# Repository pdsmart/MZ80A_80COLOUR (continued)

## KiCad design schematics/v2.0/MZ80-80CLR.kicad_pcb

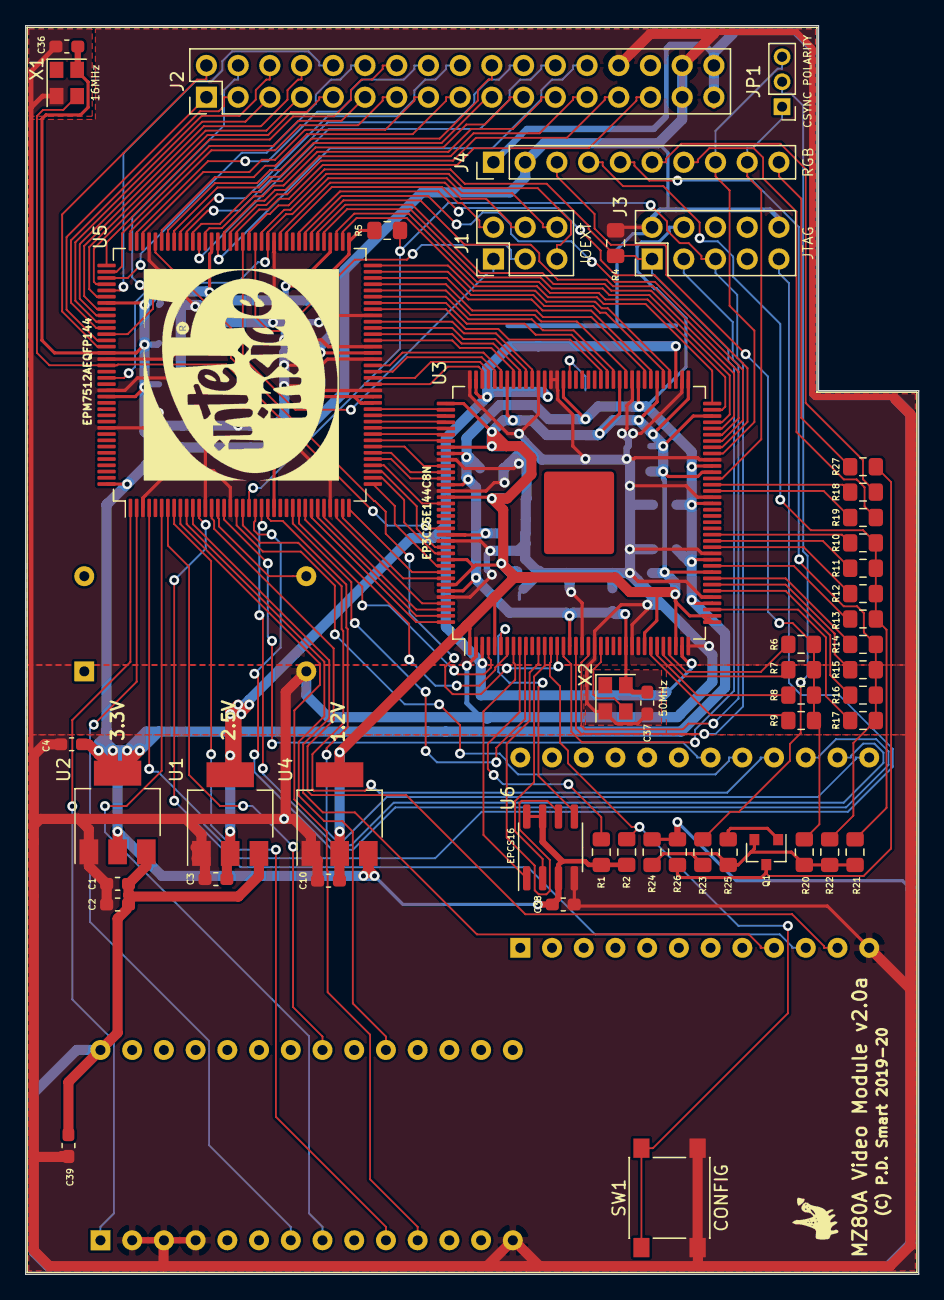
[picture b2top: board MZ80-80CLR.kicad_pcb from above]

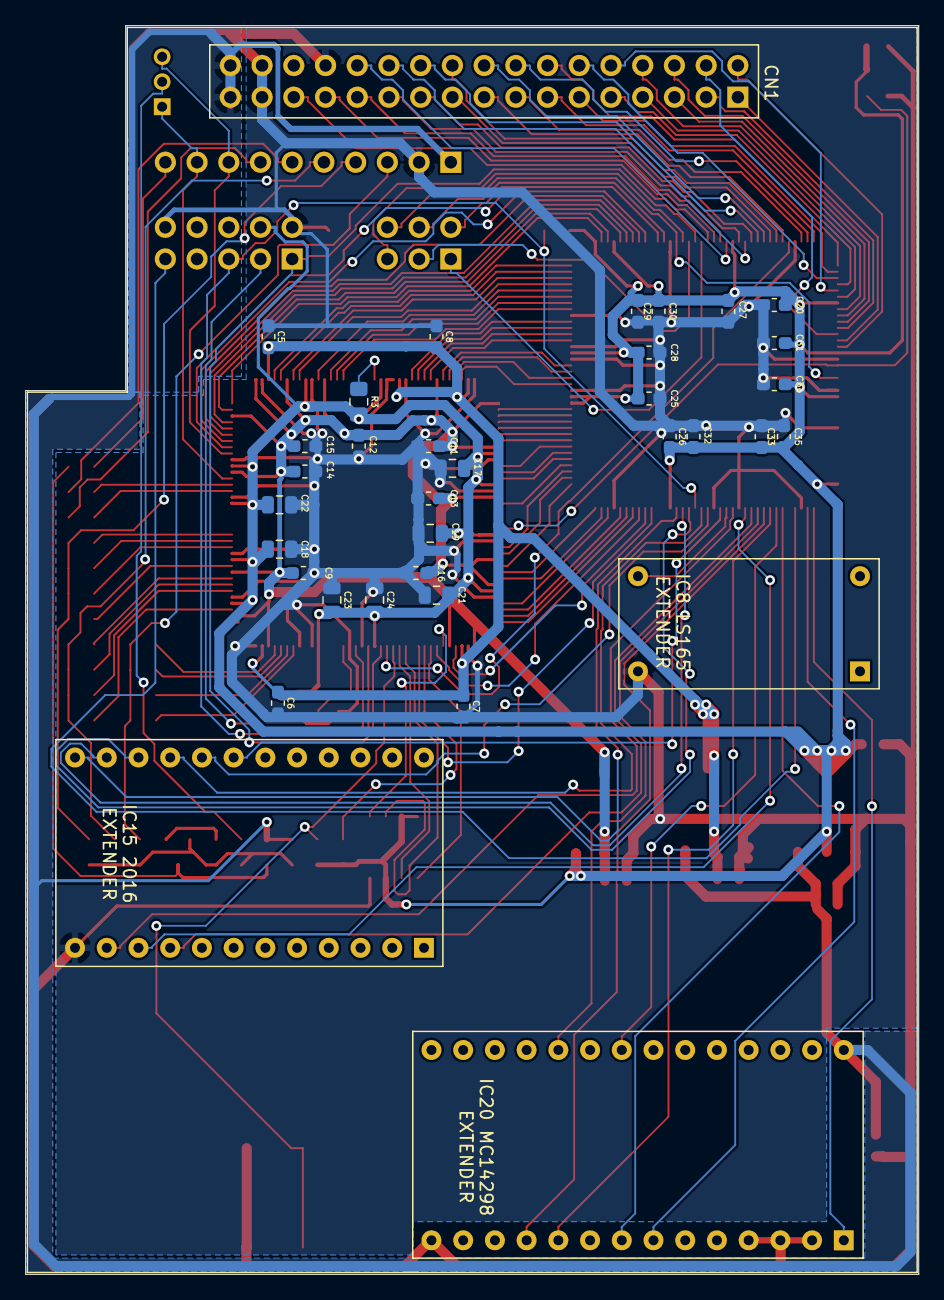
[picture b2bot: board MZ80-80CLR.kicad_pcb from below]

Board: 2 copper layers, 71.5 x 100.0 mm, 84 parts (31 on the bottom side), 141 nets.

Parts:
C1, C3, C4, C10: 10uF; C_0603_1608Metric_Pad1.05x0.95mm_HandSolder
C2, C5, C6, C7, C8, C9, C11, C12, C13, C14, C15, C16, C20, C25, C26, C27, C28, C29, C30, C31, C32, C33, C34, C35, C36, C37, C38, C39: 100nF; C_0603_1608Metric_Pad1.05x0.95mm_HandSolder
C17, C18, C19, C21, C22, C23, C24: 100nF; C_0805_2012Metric
J1: IOEXT; PinHeader_2x03_P2.54mm_Vertical
J2: M/Board CN; PinHeader_2x17_P2.54mm_Vertical
J3: JTAG; PinHeader_2x05_P2.54mm_Vertical
J4: RGB; PinHeader_1x10_P2.54mm_Vertical
JP1: CSYNC POLARITY; PinHeader_1x03_P2.00mm_Vertical
Q1: BC858; SOT-23
R1, R2, R3, R5: 10K; R_0805_2012Metric_Pad1.15x1.40mm_HandSolder
R4, R7, R11, R15, R22, R23, R24: 1K; R_0805_2012Metric_Pad1.15x1.40mm_HandSolder
R6, R10, R14: 500R; R_0805_2012Metric_Pad1.15x1.40mm_HandSolder
R8, R12, R16: 2K; R_0805_2012Metric_Pad1.15x1.40mm_HandSolder
R9, R13, R17: 4K; R_0805_2012Metric_Pad1.15x1.40mm_HandSolder
R18, R19: 120R; R_0805_2012Metric_Pad1.15x1.40mm_HandSolder
R20: 3K9; R_0805_2012Metric_Pad1.15x1.40mm_HandSolder
R21: 2K2; R_0805_2012Metric_Pad1.15x1.40mm_HandSolder
R25: 220R; R_0805_2012Metric_Pad1.15x1.40mm_HandSolder
R26, R27: 68R; R_0805_2012Metric_Pad1.15x1.40mm_HandSolder
SK1: IC15 Socket; DIP-24_W15.24mm_Socket
SK2: IC8 Socket; DIP-16_W7.62mm_Socket
SK3: IC20 Socket; DIP-28_W15.24mm_Socket
SW1: CONFIG; SW_SPST_PTS645
U1: AMS1117-2.5; SOT-223-3_TabPin2
U2: AMS1117-3.3; SOT-223-3_TabPin2
U3: EP3C25E144C8N; EQFP-144-1EP_20x20mm_P0.5mm_EP6.61x5.615mm
U4: AMS1117-1.2; SOT-223-3_TabPin2
U5: EPM7512AEQFP144; TQFP-144_20x20mm_P0.5mm
U6: EPCS16; SOIC-8_3.9x4.9mm_P1.27mm
X1: 16MHz; Oscillator_SMD_Abracon_ASE-4Pin_3.2x2.5mm
X2: 50MHz; Oscillator_SMD_Abracon_ASE-4Pin_3.2x2.5mm

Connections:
1MHZ_OUT: SK3.21, U5.7
2MHZ_OUT: SK3.19, U5.10
31.5K_OUT: SK3.11, U5.9
+1V2: C9.1, C10.1, C11.1, C12.1, C13.1, C14.1, C15.1, C16.1, U3.1, U3.5, U3.29, U3.34, U3.37, U3.38, U3.45, U3.61, U3.70, U3.73, U3.78, U3.84, U3.102, U3.109, U3.116, U3.124, U3.134, U3.138, U4.2
+2V5: C3.1, C5.1, C6.1, C7.1, C8.1, U1.2, U3.3, U3.35, U3.75, U3.96, U3.107
+3V3: C4.1, C17.1, C18.1, C19.1, C20.1, C21.1, C22.1, C23.1, C24.1, C25.1, C26.1, C27.1, C28.1, C29.1, C30.1, C31.1, C32.1, C33.1, C34.1, C35.1, C36.1, C37.1, C38.1, J3.4, R1.1, R2.1, R3.1, R5.1, U2.2, U3.17, U3.26, U3.40, U3.47, U3.56, U3.62, U3.81, U3.93, U3.117, U3.122, U3.130, U3.139, U4.3, U5.24, U5.50, U5.51, U5.58, U5.73, U5.76, U5.95, U5.115, U5.123, U5.130, U5.144, U6.3, U6.7, U6.8, X1.4, X2.4
+5V: C1.1, C2.1, C39.2, J2.33, J2.34, J4.1, R24.2, R26.2, SK3.28, U1.3, U2.3
/FPGA and CPLD Module/A0: J2.1, U5.121
/FPGA and CPLD Module/A1: J2.3, U5.119
/FPGA and CPLD Module/A2: J2.5, U5.117
/FPGA and CPLD Module/A3: J2.7, U5.114
/FPGA and CPLD Module/A4: J2.9, U5.112
/FPGA and CPLD Module/A5: J2.11, U5.110
/FPGA and CPLD Module/A6: J2.13, U5.108
/FPGA and CPLD Module/A7: J2.15, U5.106
/FPGA and CPLD Module/A8: J2.17, U5.103
/FPGA and CPLD Module/A9: J2.19, U5.101
/FPGA and CPLD Module/A10: J2.21, U5.98
/FPGA and CPLD Module/A11: J1.1, U5.90
/FPGA and CPLD Module/A12: J1.3, U5.88
/FPGA and CPLD Module/A13: J1.5, U5.87
/FPGA and CPLD Module/D0: J2.2, U5.122
/FPGA and CPLD Module/D1: J2.4, U5.120
/FPGA and CPLD Module/D2: J2.6, U5.118
/FPGA and CPLD Module/D3: J2.8, U5.116
/FPGA and CPLD Module/D4: J2.10, U5.113
/FPGA and CPLD Module/D5: J2.12, U5.111
/FPGA and CPLD Module/D6: J2.14, U5.109
/FPGA and CPLD Module/D7: J2.16, U5.107
/FPGA and CPLD Module/MB_LOAD: J2.18, U5.100
/FPGA and CPLD Module/MB_SYNCH: J2.24, U5.97
/FPGA and CPLD Module/MB_VIDEO: J2.20, U5.102
/FPGA and CPLD Module/TBA0: U3.87, U5.65
/FPGA and CPLD Module/TBA1: U3.86, U5.66
/FPGA and CPLD Module/TBA2: U3.85, U5.67
/FPGA and CPLD Module/TBA3: U3.83, U5.68
/FPGA and CPLD Module/TBA4: U3.80, U5.69
/FPGA and CPLD Module/TBA5: U3.79, U5.70
/FPGA and CPLD Module/TBA6: U3.77, U5.71
/FPGA and CPLD Module/TBA7: U3.76, U5.72
/FPGA and CPLD Module/TBA8: U3.72, U5.74
/FPGA and CPLD Module/TBA9: U3.71, U5.75
/FPGA and CPLD Module/VADDR0: U3.4, U5.28
/FPGA and CPLD Module/VADDR1: U3.7, U5.29
/FPGA and CPLD Module/VADDR2: U3.144, U5.30
/FPGA and CPLD Module/VADDR3: U3.143, U5.31
/FPGA and CPLD Module/VADDR4: U3.142, U5.32
/FPGA and CPLD Module/VADDR5: U3.141, U5.34
/FPGA and CPLD Module/VADDR6: U3.137, U5.35
/FPGA and CPLD Module/VADDR7: U3.136, U5.36
/FPGA and CPLD Module/VADDR8: U3.135, U5.37
/FPGA and CPLD Module/VADDR9: U3.133, U5.38
/FPGA and CPLD Module/VADDR10: U3.132, U5.39
/FPGA and CPLD Module/VADDR11: U3.125, U5.40
/FPGA and CPLD Module/VADDR12: U3.121, U5.41
/FPGA and CPLD Module/VADDR13: U3.120, U5.42
/FPGA and CPLD Module/VDATA0: U3.98, U5.63
/FPGA and CPLD Module/VDATA1: U3.99, U5.62
/FPGA and CPLD Module/VDATA2: U3.100, U5.61
/FPGA and CPLD Module/VDATA3: U3.101, U5.60
/FPGA and CPLD Module/VDATA4: U3.103, U5.56
/FPGA and CPLD Module/VDATA5: U3.104, U5.55
/FPGA and CPLD Module/VDATA6: U3.105, U5.54
/FPGA and CPLD Module/VDATA7: U3.106, U5.53
/FPGA and CPLD Module/VHSY_OUT: U3.67, U5.79
/FPGA and CPLD Module/VSRVIDEO_OUT: U3.65, U5.81
/FPGA and CPLD Module/VSYNCH_OUT: U3.68, U5.78
/FPGA and CPLD Module/~CS~: J2.27, U5.92
/FPGA and CPLD Module/~GT~: J2.25, U5.93
/FPGA and CPLD Module/~IORQ~: J1.4, U5.84
/FPGA and CPLD Module/~MB_HBLNK~: J2.26, U5.94
/FPGA and CPLD Module/~MB_V-HBLNK~: J2.22, U5.99
/FPGA and CPLD Module/~MEM_CS~: J1.2, U5.83
/FPGA and CPLD Module/~RD~: J2.29, U5.91
/FPGA and CPLD Module/~RESET~: J1.6, U5.86, U5.127
/FPGA and CPLD Module/~VCS~: U3.113, U5.46
/FPGA and CPLD Module/~VGT~: U3.112, U5.47
/FPGA and CPLD Module/~VHBLNK_OUT~: U3.66, U5.80
/FPGA and CPLD Module/~VIORQ~: U3.115, U5.44
/FPGA and CPLD Module/~VMEM_CS~: U3.119, U5.43
/FPGA and CPLD Module/~VRD~: U3.114, U5.45
/FPGA and CPLD Module/~VRESET~: U3.110, U5.49
/FPGA and CPLD Module/~VVBLNK_OUT~: U3.69, U5.77
/FPGA and CPLD Module/~VVRAM_CS_IN~: U3.10, U5.27
/FPGA and CPLD Module/~VWR~: U3.111, U5.48
/FPGA and CPLD Module/~WR~: J2.23, U5.96
CSYNC: J4.9, JP1.1, U3.60
GNDPWR: C1.2, C2.2, C3.2, C4.2, C5.2, C6.2, C7.2, C8.2, C9.2, C10.2, C11.2, C12.2, C13.2, C14.2, C15.2, C16.2, C17.2, C18.2, C19.2, C20.2, C21.2, C22.2, C23.2, C24.2, C25.2, C26.2, C27.2, C28.2, C29.2, C30.2, C31.2, C32.2, C33.2, C34.2, C35.2, C36.2, C37.2, C38.2, C39.1, J2.28, J2.31, J2.32, J3.2, J3.10, J4.2, R4.1, SK1.12, SK2.8, SK3.2, SK3.3, SK3.4, SK3.14, SW1.2, U1.1, U2.1, U3.2, U3.19, U3.21, U3.27, U3.36, U3.41, U3.48, U3.57, U3.63, U3.74, U3.82, U3.94, U3.95, U3.97, U3.108, U3.118, U3.123, U3.131, U3.140, U4.1, U5.3, U5.13, U5.17, U5.33, U5.52, U5.57, U5.59, U5.64, U5.85, U5.105, U5.124, U5.129, U5.135, U6.4, X1.2, X2.2
HSY_OUT: SK3.7, U5.2
unnamed: J3.1, R4.2, U3.16, U5.89
unnamed: J3.3, U3.20
unnamed: J3.5, R5.2, U3.18, U5.20
unnamed: J3.9, U5.4
unnamed: J4.3, R6.1, R7.1, R8.1, R9.1, R20.2
unnamed: J4.4, R10.1, R11.1, R12.1, R13.1, R21.2
unnamed: J4.5, R14.1, R15.1, R16.1, R17.1, R22.2
unnamed: J4.6, R18.1
unnamed: J4.7, R19.1
unnamed: J4.10, R27.2
unnamed: JP1.2, R23.2
unnamed: Q1.1, R25.1
unnamed: Q1.2, R20.1, R21.1, R22.1, R23.1, R24.1, R25.2
unnamed: Q1.3, R26.1, R27.1
unnamed: R1.2, U3.9
unnamed: R2.2, SW1.1, U3.14
unnamed: R3.2, U3.92
unnamed: U3.6, U6.5
unnamed: U3.8, U6.1
unnamed: U3.12, U6.6
unnamed: U3.13, U6.2
unnamed: U3.15, U5.104
unnamed: U3.22, X2.3
unnamed: U3.129, U5.125, X1.3
SRVIDEO_OUT: SK2.9, U5.15
SYNCH_OUT: SK3.10, U5.8
VGA_B0: R9.2, U3.30
VGA_B1: R8.2, U3.31
VGA_B2: R7.2, U3.32
VGA_B3: R6.2, U3.33
VGA_G0: R17.2, U3.39
VGA_G1: R16.2, U3.42
VGA_G2: R15.2, U3.43
VGA_G3: R14.2, U3.44
VGA_HS: R18.2, U3.59
VGA_R0: R13.2, U3.46
VGA_R1: R12.2, U3.49
VGA_R2: R11.2, U3.50
VGA_R3: R10.2, U3.51
VGA_VS: R19.2, U3.58
VRAMD0: SK1.9, U5.11
VRAMD1: SK1.10, U5.12
VRAMD2: SK1.11, U5.14
VRAMD3: SK1.13, U5.23
VRAMD4: SK1.14, U5.22
VRAMD5: SK1.15, U5.21
VRAMD6: SK1.16, U5.19
VRAMD7: SK1.17, U5.18
~CSYNC~: J4.8, JP1.3, U3.64
~HBLNK_OUT~: SK3.1, U5.1
~VBLNK_OUT~: SK3.8, U5.6
~VRAM_CS_IN~: SK1.18, U5.16

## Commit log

2019-10-25 First push
2019-11-11 Set theme jekyll-theme-tactile
2020-03-02 Attributes
2020-03-24 Added CGROM details
2020-03-24 Removed temp file
2020-07-04 WIP Video Module v2
2020-07-04 Updated schematics
2020-07-05 Added docker
2020-07-30 Tweaks to the CGROM for tranZPUter SW MZ700 mode
2020-09-02 Initial cut of the Video Module. Basic design works but on mode switch there is a sync issue which needs resolving. Need to test out the MZ80B pixel graphics
2020-09-04 Initial release of the Video Module
2020-09-04 Forgot to save!!
2020-09-05 Updates for better compatibility with the tranZPUter v2.2 board and mainboard overclocking
2020-09-08 Changes to the serialiser in order to get the pixel mapped graphics working - needs more changes as it isnt reliable at 4MHz mainboard frequency
2020-11-02 New video module developments
2020-11-08 Updates to Video Module
2020-11-10 Bug fixes and tweaks
2020-11-14 Updates to video logic
2021-02-06 Added schematics, kicad and pcb gerber files
2021-02-18 Re-organisation of CAD files, previous version not useable as files missing
2021-02-19 Tidy
2021-08-22 Updates not checked in
